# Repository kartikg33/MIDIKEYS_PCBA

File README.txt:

BoM
---

#	Component							Qty		Vendor
-	---------							---		------
1	MIDI KEYS Right PCB (KEY201)		3 		OSH Park
2	Resistor 0603 10K					36
3	Resistor 0603 82R					36
4	IDC Socket 50-Way (3M 8550-4500)	3
5 	Cherry MX Red						36
6   LED 3mm Red							21					
7	LED 3mm Blue						15

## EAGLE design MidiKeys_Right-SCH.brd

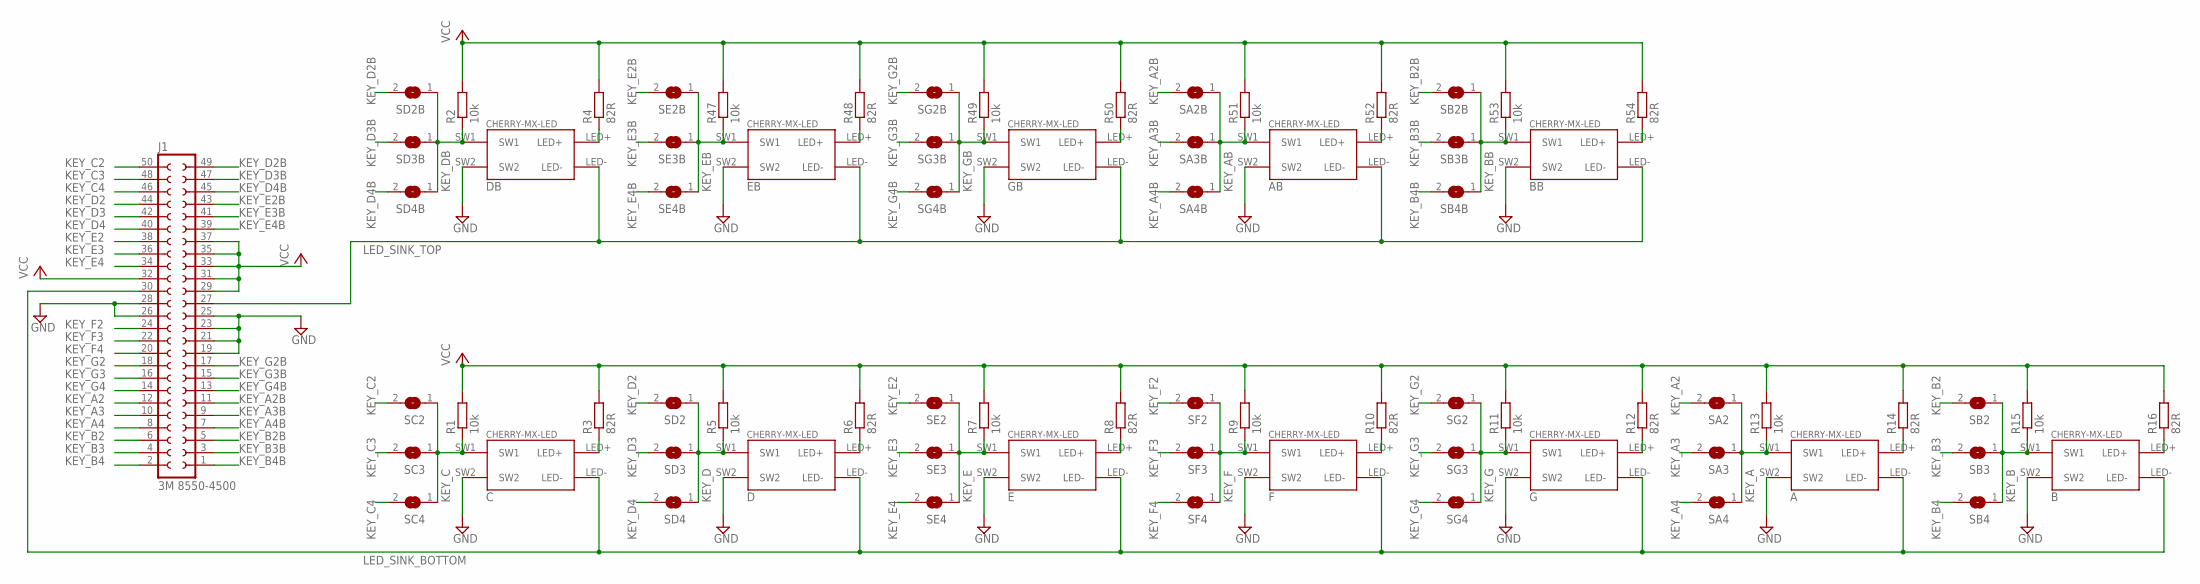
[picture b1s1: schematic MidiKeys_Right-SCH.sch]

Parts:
A: CHERRY-MX-LED
AB: CHERRY-MX-LED
B: CHERRY-MX-LED
BB: CHERRY-MX-LED
C: CHERRY-MX-LED
D: CHERRY-MX-LED
DB: CHERRY-MX-LED
E: CHERRY-MX-LED
EB: CHERRY-MX-LED
F: CHERRY-MX-LED
G: CHERRY-MX-LED
GB: CHERRY-MX-LED
J1: 3M 8550-4500; S50V
R1, R2, R5, R7, R9, R11, R13, R15, R47, R49, R51, R53: 10k; R0603
R3, R4, R6, R8, R10, R12, R14, R16, R48, R50, R52, R54: 82R; R0603
SA2, SA2B, SA3, SA3B, SA4, SA4B: SJ
SB2, SB2B, SB3, SB3B, SB4, SB4B: SJ
SC2, SC3, SC4: SJ
SD2, SD2B, SD3, SD3B, SD4, SD4B: SJ
SE2, SE2B, SE3, SE3B, SE4, SE4B: SJ
SF2, SF3, SF4: SJ
SG2, SG2B, SG3, SG3B, SG4, SG4B: SJ

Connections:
GND: A.SW2, AB.SW2, B.SW2, BB.SW2, C.SW2, D.SW2, DB.SW2, E.SW2, EB.SW2, F.SW2, G.SW2, GB.SW2, J1.19, J1.21, J1.23, J1.25, J1.26, J1.28
KEY_A: A.SW1, R13.1, SA2.1, SA3.1, SA4.1
KEY_A2: J1.12, SA2.2
KEY_A2B: J1.11, SA2B.2
KEY_A3: J1.10, SA3.2
KEY_A3B: J1.9, SA3B.2
KEY_A4: J1.8, SA4.2
KEY_A4B: J1.7, SA4B.2
KEY_AB: AB.SW1, R51.1, SA2B.1, SA3B.1, SA4B.1
KEY_B: B.SW1, R15.1, SB2.1, SB3.1, SB4.1
KEY_B2: J1.6, SB2.2
KEY_B2B: J1.5, SB2B.2
KEY_B3: J1.4, SB3.2
KEY_B3B: J1.3, SB3B.2
KEY_B4: J1.2, SB4.2
KEY_B4B: J1.1, SB4B.2
KEY_BB: BB.SW1, R53.1, SB2B.1, SB3B.1, SB4B.1
KEY_C: C.SW1, R1.1, SC2.1, SC3.1, SC4.1
KEY_C2: J1.50, SC2.2
KEY_C3: J1.48, SC3.2
KEY_C4: J1.46, SC4.2
KEY_D: D.SW1, R5.1, SD2.1, SD3.1, SD4.1
KEY_D2: J1.44, SD2.2
KEY_D2B: J1.49, SD2B.2
KEY_D3: J1.42, SD3.2
KEY_D3B: J1.47, SD3B.2
KEY_D4: J1.40, SD4.2
KEY_D4B: J1.45, SD4B.2
KEY_DB: DB.SW1, R2.1, SD2B.1, SD3B.1, SD4B.1
KEY_E: E.SW1, R7.1, SE2.1, SE3.1, SE4.1
KEY_E2: J1.38, SE2.2
KEY_E2B: J1.43, SE2B.2
KEY_E3: J1.36, SE3.2
KEY_E3B: J1.41, SE3B.2
KEY_E4: J1.34, SE4.2
KEY_E4B: J1.39, SE4B.2
KEY_EB: EB.SW1, R47.1, SE2B.1, SE3B.1, SE4B.1
KEY_F: F.SW1, R9.1, SF2.1, SF3.1, SF4.1
KEY_F2: J1.24, SF2.2
KEY_F3: J1.22, SF3.2
KEY_F4: J1.20, SF4.2
KEY_G: G.SW1, R11.1, SG2.1, SG3.1, SG4.1
KEY_G2: J1.18, SG2.2
KEY_G2B: J1.17, SG2B.2
KEY_G3: J1.16, SG3.2
KEY_G3B: J1.15, SG3B.2
KEY_G4: J1.14, SG4.2
KEY_G4B: J1.13, SG4B.2
KEY_GB: GB.SW1, R49.1, SG2B.1, SG3B.1, SG4B.1
LED_SINK_BOTTOM: A.LED-, B.LED-, C.LED-, D.LED-, E.LED-, F.LED-, G.LED-, J1.30
LED_SINK_TOP: AB.LED-, BB.LED-, DB.LED-, EB.LED-, GB.LED-, J1.27
unnamed: D.LED+, R6.1
unnamed: E.LED+, R8.1
unnamed: F.LED+, R10.1
unnamed: DB.LED+, R4.1
unnamed: C.LED+, R3.1
unnamed: G.LED+, R12.1
unnamed: A.LED+, R14.1
unnamed: B.LED+, R16.1
unnamed: EB.LED+, R48.1
unnamed: GB.LED+, R50.1
unnamed: AB.LED+, R52.1
unnamed: BB.LED+, R54.1
VCC: J1.29, J1.31, J1.32, J1.33, J1.35, J1.37, R1.2, R2.2, R3.2, R4.2, R5.2, R6.2, R7.2, R8.2, R9.2, R10.2, R11.2, R12.2, R13.2, R14.2, R15.2, R16.2, R47.2, R48.2, R49.2, R50.2, R51.2, R52.2, R53.2, R54.2

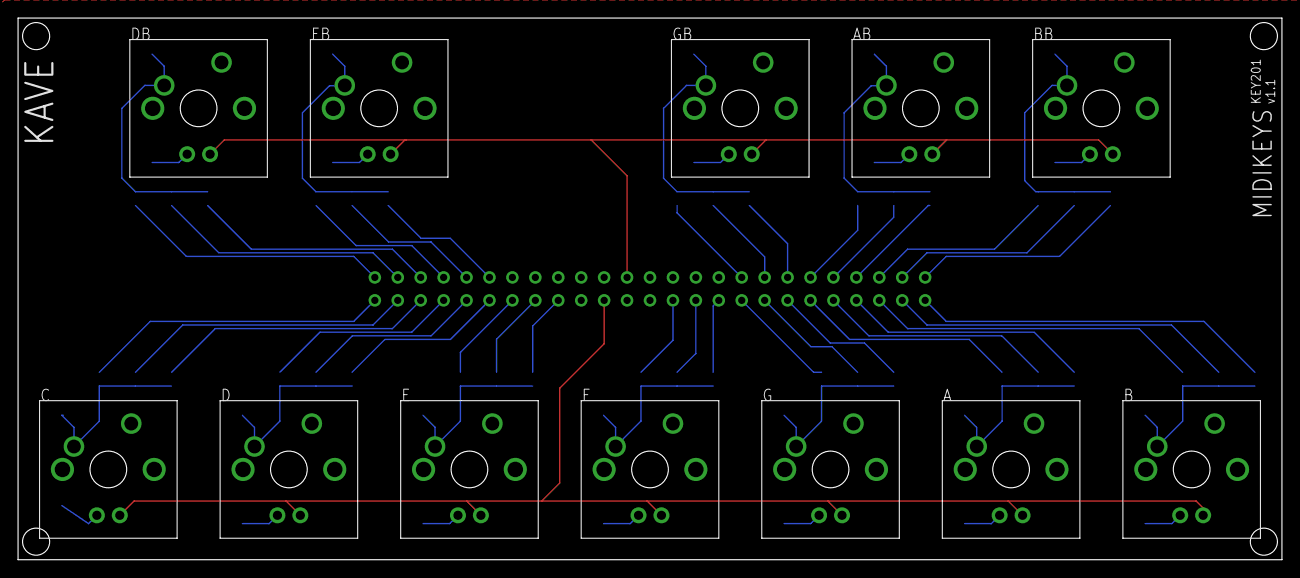
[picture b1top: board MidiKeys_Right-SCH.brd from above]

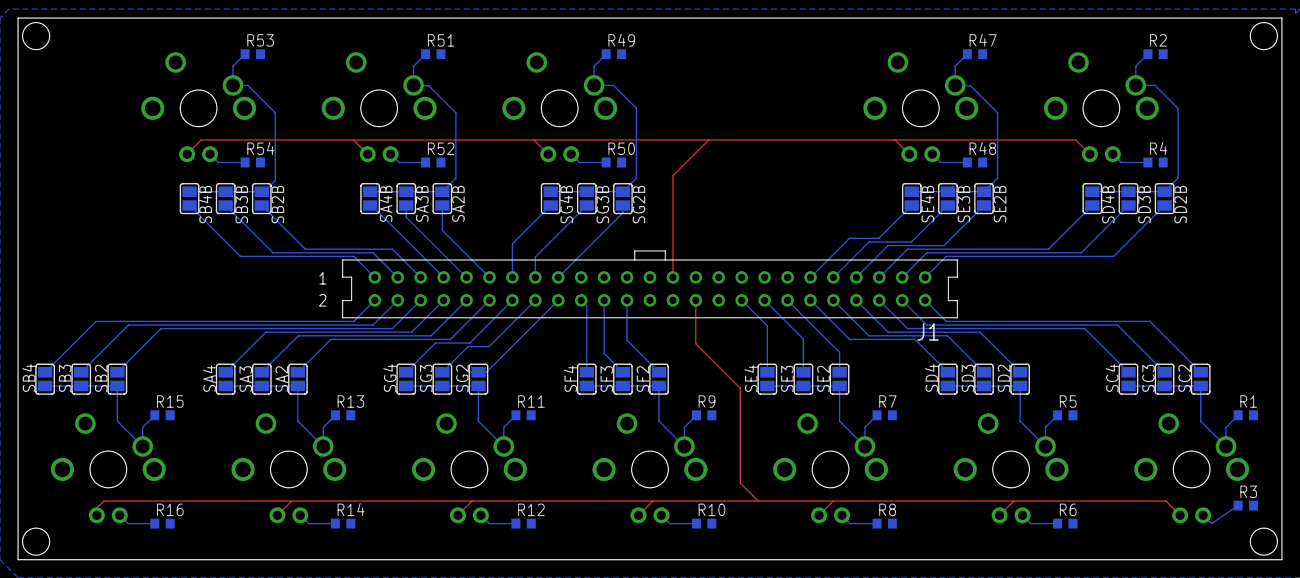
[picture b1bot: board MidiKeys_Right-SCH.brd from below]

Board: 2 copper layers, 140.0 x 60.0 mm, 73 parts (61 on the bottom side), 64 nets.

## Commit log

2018-05-07 initial commit of existing project to git
2018-05-07 added all key nets
2018-05-07 cleaned up keys - now adding all of them to schematic
2018-05-07 created bottom row of keys in schematic
2018-05-07 wired up all keys and assigned net and component names@
2018-05-07 regenerated board
2018-05-07 updated switch library part
2018-05-07 updated eagle to 9.0.1
2018-05-19 added transistor led driver circuit@
2018-05-19 synced board to schematic
2018-05-19 updated project file
2018-05-19 added OSH Park drc and cam plugin to eagle and updated board outline to required dimensions
2018-05-22 removed arduino shield and transistors. added 50way idc connector and solder bridges to manually connect up the correct octave. board size now 140x60. sch done. layout started
2018-05-22 fixed all ERC errors and started layout.
2018-05-22 modified layout slightly
2018-05-23 placed solder bridges in correct places
2018-05-23 complete layout done
2018-05-23 ordered pcb via oshpark
2018-06-08 added readme with bill of materials
